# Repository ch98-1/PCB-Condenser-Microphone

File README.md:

# PCB-Condenser-Microphone
Basic Condenser microphone kit that uses the PCB as a backplate. It is highly recommended to get the pcb manifactured with ENIG finish for flatness and corrosion resistance. For standalone use, it is recommended to go with the shielded design. For the opamp, any 8SOICopamp with the same pinout as LM358 should be able to replace the one on the board, and lower noise opamp such as OPA1678 is recommended for less static.
For more information, visit corwinh.com/pcm or read the assembly instructions in the PCB-Condenser-Microphone.pdf file in the instruction-manual directory.

**License**

All files are licensed under [zlib license](https://opensource.org/licenses/Zlib) unless noted otherwise.
Some KiCad Library Files (PCB-Condenser-Microphone/PCB-Condenser-Microphone-cache.lib PCB-Condenser-Microphone-Backplate/PCB-Condenser-Microphone-Backplate-cache.lib and PCB-Condenser-Microphone-Clamp/PCB-Condenser-Microphone-Clamp-cache.lib) are licensed under [KiCad Libraries License] (http://kicad-pcb.org/libraries/license/)

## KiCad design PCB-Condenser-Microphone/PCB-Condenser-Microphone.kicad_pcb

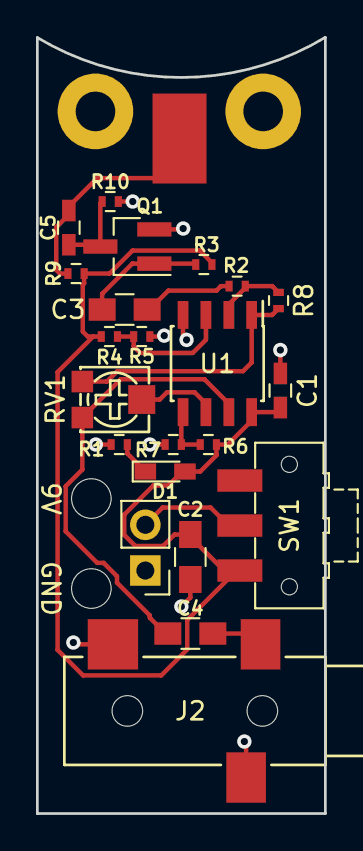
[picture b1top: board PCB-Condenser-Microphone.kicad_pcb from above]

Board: 2 copper layers, 16.0 x 43.1 mm, 25 parts (0 on the bottom side), 15 nets.

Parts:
C1: 0.47uF; C_0603_HandSoldering
C2, C3, C4: 10uF; C_0805_HandSoldering
C5: 680pF; C_0603_HandSoldering
D1: LED; LED_0603_HandSoldering
J1: Conn_01x02; Pin_Header_Straight_1x02_Pitch2.54mm
J2: SJ-3523-SMT; SJ-3523-SMT-TR
MK1: Microphone_Condenser; Condenser-Microphone-Backplate-30mm-Single-mount
MT1, MT2: Strain Relief; MountingHole_2.2mm_M2
Q1: Q_NJFET_DSG; SOT-23_Handsoldering
R1, R2: 1k; R_0402
R3: 10K; R_0402
R4, R5, R6, R7: 10k; R_0402
R8: 100k; R_0402
R9, R10: 100M; R_0402
RV1: 100k; TC33X
SW1: SW_SPDT; SW_SPDT_CK-JS102011SAQN
U1: LM358; SOIC-8_3.9x4.9mm_Pitch1.27mm

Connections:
+9V: C1.2, C2.2, D1.2, R3.1, R4.1, R6.1, R9.1, SW1.1, U1.8
GND: C1.1, C2.1, J1.1, J2.1, J2.3, MK1.1, Q1.2, R1.2, R5.2, R7.2, R10.2, U1.4
unnamed: C3.1, R2.2
unnamed: C3.2, Q1.1, R3.2
unnamed: C4.1, J2.2
unnamed: C4.2, RV1.3, U1.7
unnamed: C5.1, Q1.3, R10.1
unnamed: C5.2, MK1.2, R9.2
unnamed: D1.1, R1.1
unnamed: J1.2, SW1.2
unnamed: R2.1, R8.2, U1.2
unnamed: R4.2, R5.1, U1.3
unnamed: R6.2, R7.1, U1.5
unnamed: R8.1, RV1.1, U1.1
unnamed: RV1.2, U1.6

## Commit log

2018-03-10 Added License
2018-03-10 Created project file
2018-03-11 Created backplate and clamp
2018-03-13 Created schimatic and added digikey BOM
2018-03-13 Added Titles
2018-03-13 Layd out pcb and added OSHW logo
2018-03-13 Routed PCB
2018-03-13 Generated Gerber
2018-03-14 Fixed an unconnected trace
2018-03-14 Fixed pcb outline and regenerated gerber
2018-03-14 Removed silkscreen from clamp
2018-03-25 Added spacer for printout
2018-03-26 Updated mic backplate to be double sided
2018-03-26 Updated schimatic to have fet preamp
2018-03-26 Updated circuit to match the jfet
2018-03-26 Uodated JFET
2018-03-27 Added back OSHW logo to preamp
2018-03-27 Added recomendation to manifacture the pcb with ENIG finish
2018-03-29 Updated files for new library
2018-04-04 Switched ground and bias on microphone preamp
2018-04-04 Added BOM for shielded mic assembly
2018-04-04 Updated design to use same bolt for shielded version
2018-04-05 Added seperate BOM for fasteners
2018-04-15 Chenged components after prototyping
2018-04-16 Added bom for all other components
2018-04-21 Created instruction manual file
2018-06-29 fixed a link

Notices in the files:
PCB-Condenser-Microphone/PCB-Condenser-Microphone.kicad_pcb:
(c) 2018 Corwin Hansen
